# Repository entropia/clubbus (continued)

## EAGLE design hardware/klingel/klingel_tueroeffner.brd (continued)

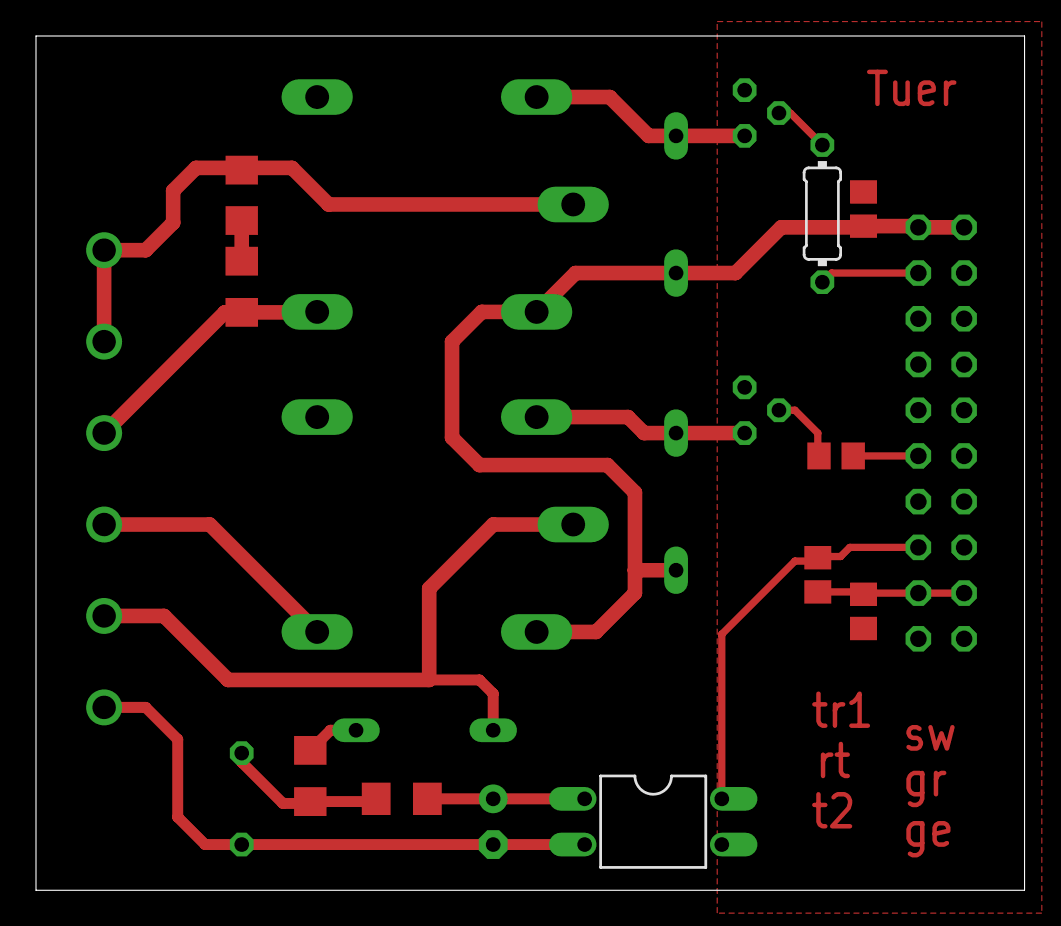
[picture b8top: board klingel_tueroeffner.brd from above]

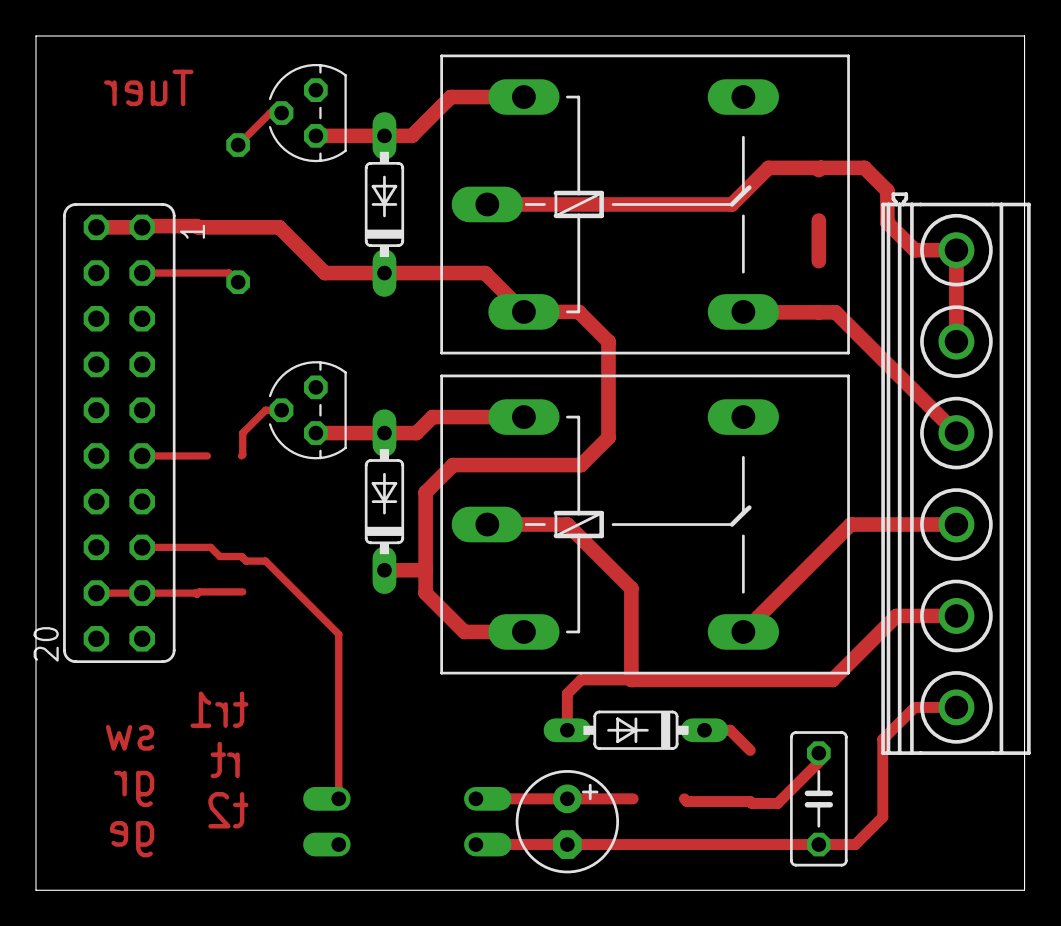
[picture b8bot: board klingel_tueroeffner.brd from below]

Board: 2 copper layers, 54.9 x 47.5 mm, 21 parts (11 on the bottom side), 19 nets.

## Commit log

2012-10-10 import existing schematics
2012-10-10 added the DALI interface
2012-10-10 put the hardware designs in a folder, where you would rather expect them to be
2012-10-10 added the bus power switch
2012-10-10 added the missing resistor values and a reference to the site with the original idea
2012-10-15 changed some resistor values
2012-10-25 added the resistor values for bus voltage measurement
2012-11-15 Add protocol spec
2012-11-15 add README
2012-11-27 add layout for door opener
2012-11-28 add rs232 interface
2012-11-30 change the package of the max202 and add some documentation
2012-12-05 change the value of the capacitor on the bus to be in spec
2012-12-09 release canpipe
2013-01-18 add snapshot of EDEN CLI
2013-02-02 add schematics for rfm12 module
2013-03-10 Fix a typo in the protocol spec
    CAN-IDs are 29 bits long. Thus, the event ID of a globally assigned event
    is only 27 bits long.
2013-03-10 Document the currently assigned well-known events
2013-03-10 add a nonisolated version of the raspberry pi to iomodul adapter
2013-03-11 consolidate busfahrer_pi-variants
2013-03-11 add busfahrer_pi-variant without iomodul
    This variant of busfahrer_pi exposes a MCP2515 and the power switch
    directly to the Raspberry.
2013-03-12 move the classic busfahrer_pi design to a new location
2013-03-12 some fixes
2014-03-03 [utils] add kontrollsucht webinterface
2015-01-11 add current version of iomodul2
2015-01-27 Add hardware for Fensterkontakte.
